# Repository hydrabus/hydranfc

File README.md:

HydraNFC Shield v1 and HydraNFC Antenna
========

HydraNFC hardware shield v1

The HydraNFC is an NFC shield hardware to sniff, read/write or emulate any 13.56MHz NFC tags for anyone interested in debugging/hacking/developing for NFC.
It has been designed to be used with HydraBus see https://github.com/hydrabus/hydrabus but can also be used with other MCU.

Open source code firmware(For HydraBus), is available see
https://github.com/hydrabus/hydrafw

Wiki for HydraFW: https://github.com/hydrabus/hydrafw/wiki

Tutorial with HydraBus + HydraNFC  (using HydraFW v0.5 beta):
* Initialize GPIO & SPI to communicate with TRF7970A/HydraNFC
* Initialize & read ISO15693/Vicinity Tag
* Initialize & read ISO14443A/Mifare Tag
* Use TRF7970A commands (SLOS743K – August 2011 – revised April 2014)
* For more details see 
https://github.com/hydrabus/hydrafw/wiki/HydraFW-HydraNFC-v1-guide
https://github.com/hydrabus/hydrafw/wiki/HydraFW-HydraNFC-v1.x-TRF7970A-Tutorial

Tutorial to use HydraNFC and understand how work the NFC chipset (TRF7970A) with BusPirate or any other hardware with SPI:
* See http://bvernoux.blogspot.fr/2012/01/nfc-ti-trf7970a-breakout-board-v10-for.html

For more details on the hardware see also http://hydrabus.com/hydranfc-1-0-specifications

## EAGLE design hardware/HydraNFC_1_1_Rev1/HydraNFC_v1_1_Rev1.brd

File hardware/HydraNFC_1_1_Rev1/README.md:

HydraNFC Shield Schematic and Board CadSoft Eagle 6.x
========

This directory contains HydraNFC shield Schematic and Board for CadSoft Eagle 6.x

HydraNFC shield: Hardware license [CC BY-NC 4.0](https://creativecommons.org/licenses/by-nc/4.0/) (for commercial license contact info@hydrabus.com)

For more details on the hardware see also http://hydrabus.com/?page_id=30

HydraNFC shield PCB Top

HydraNFC shield PCB Bottom

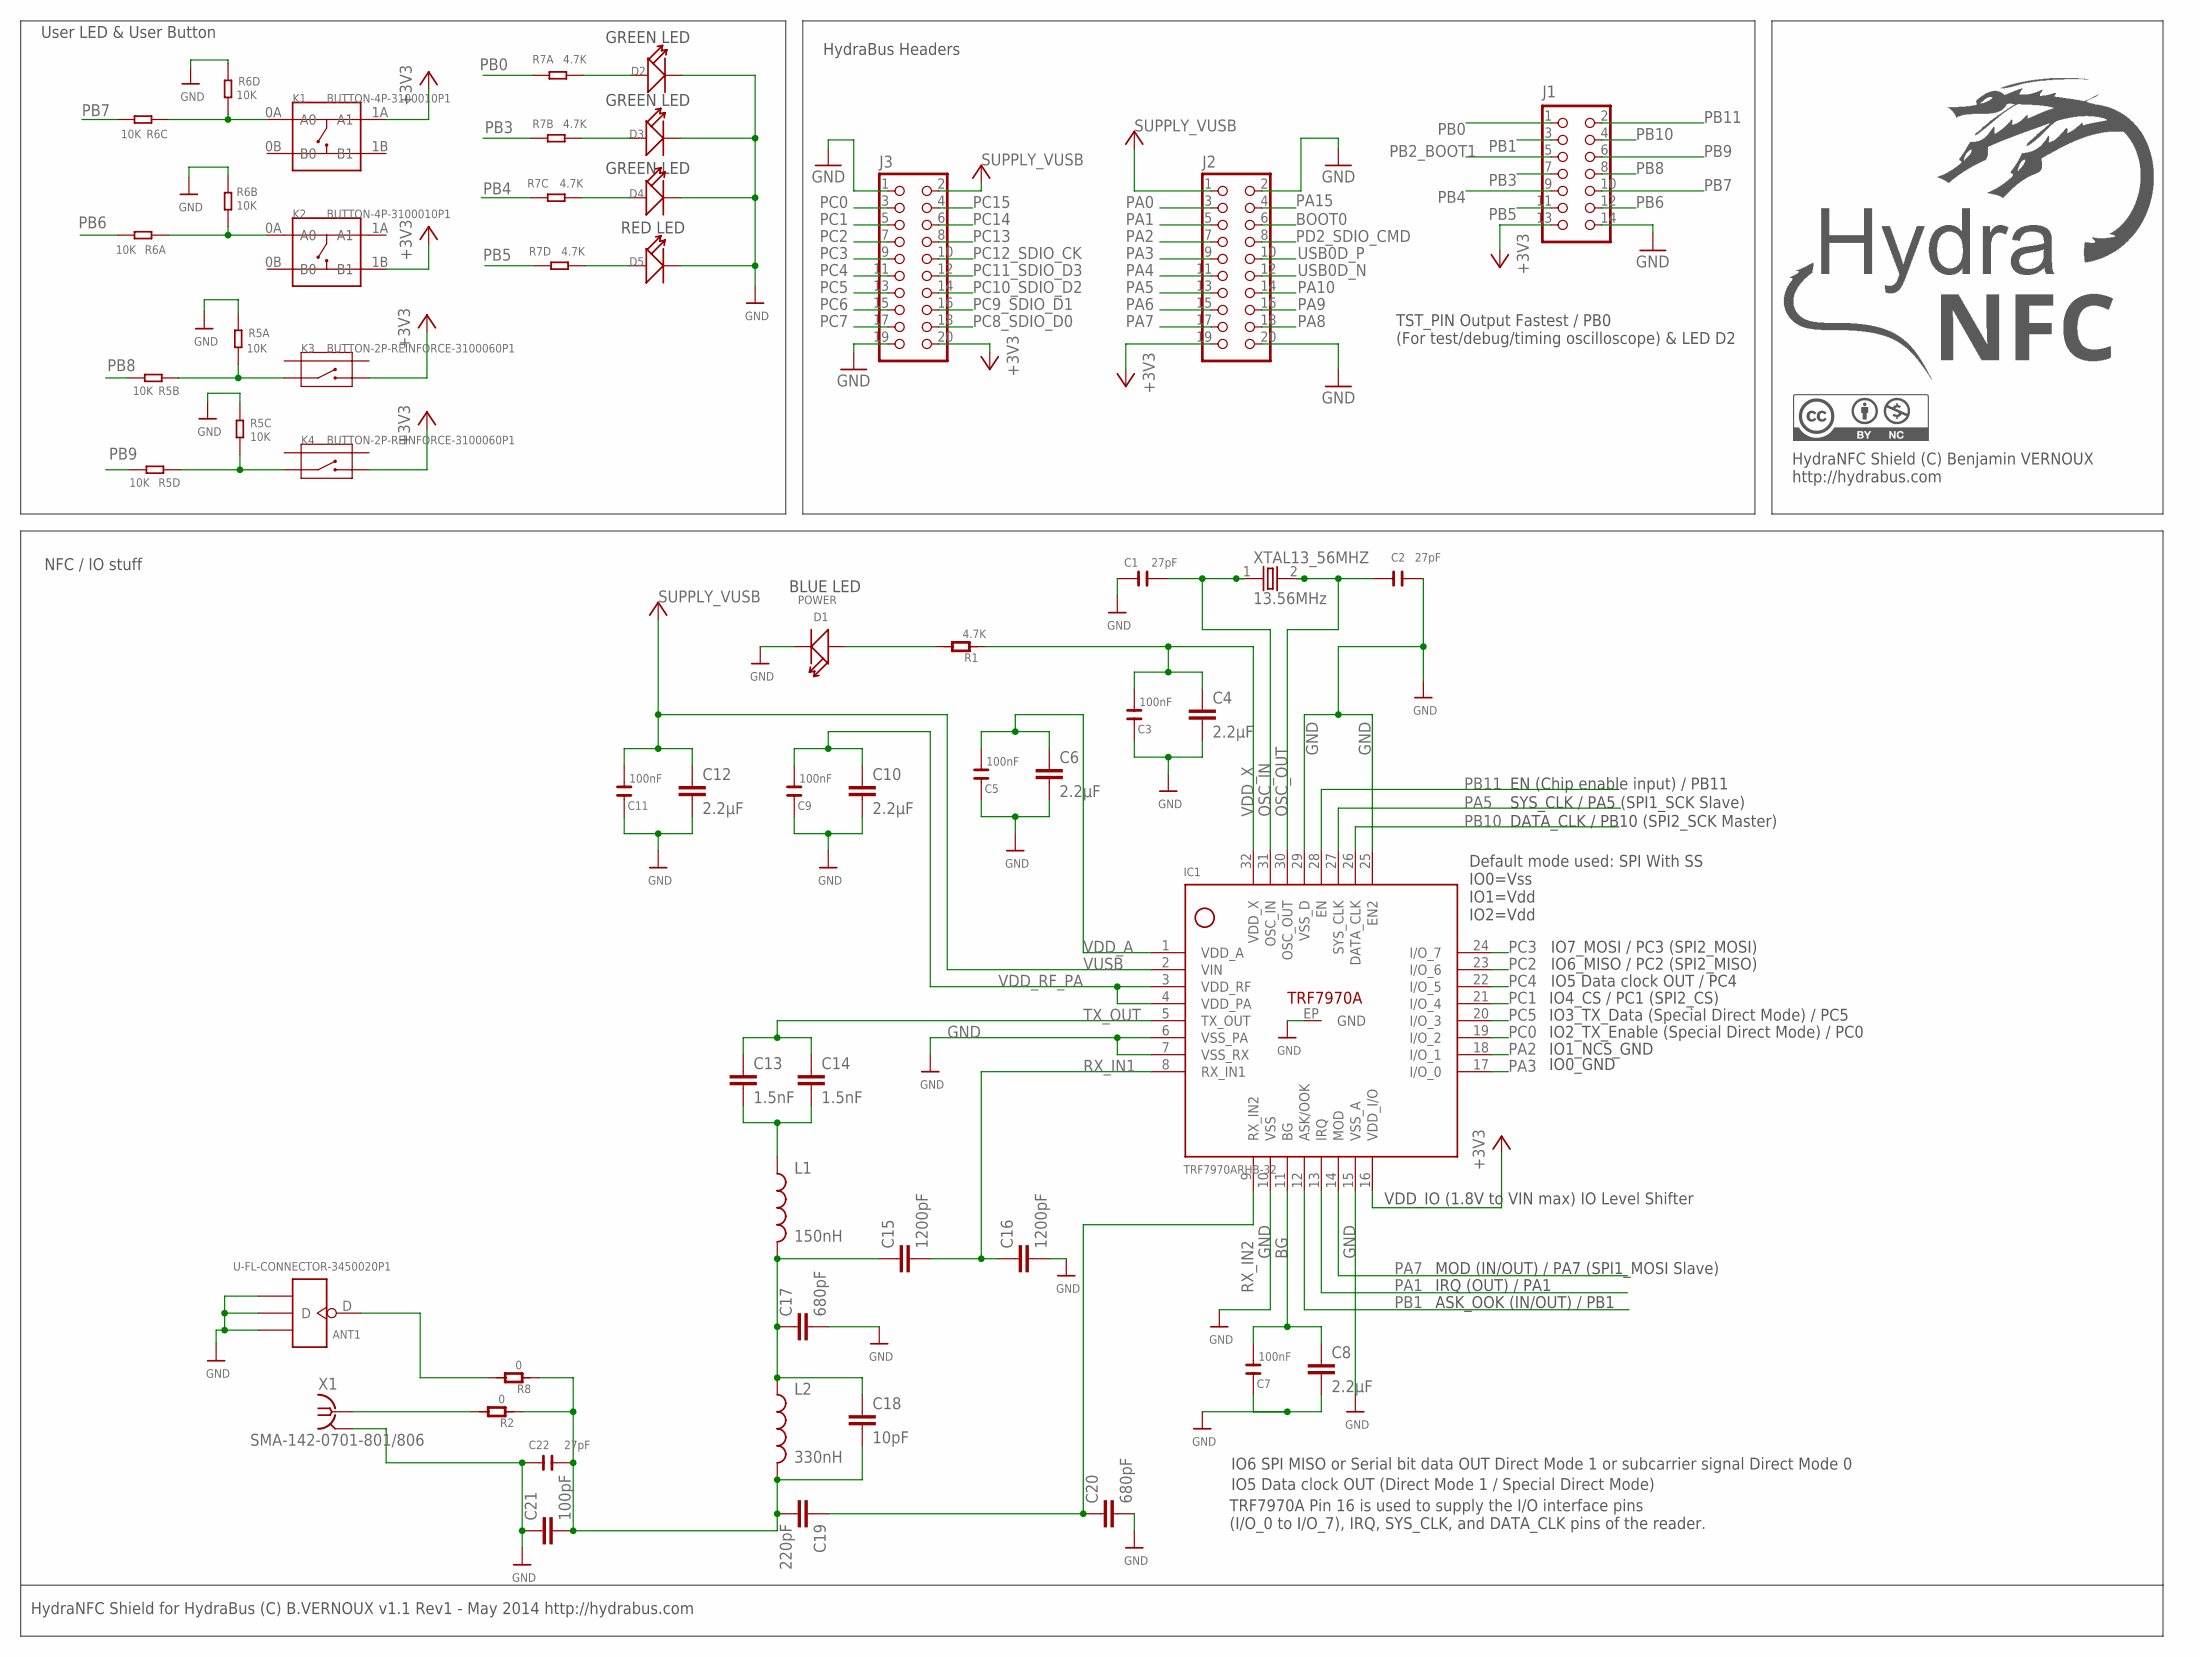
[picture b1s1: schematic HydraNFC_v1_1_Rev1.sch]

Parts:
ANT1: U-FL-CONNECTOR-3450020P1; U-FL
C1, C2, C22: 27pF; C0603
C3, C5, C7, C9, C11: 100nF; C0603
C4, C6, C8, C10, C12: 2.2µF; C805
C13, C14: 1.5nF; C805
C15, C16: 1200pF; C805
C17, C20: 680pF; C805
C18: 10pF; C805
C19: 220pF; C805
C21: 100pF; C805
D1: POWER; LED0603
D2, D3, D4, D5: LED; LED0603
IC1: TRF7970ARHB-32; TRF7970A
J1: HYDRABUS_SHIELD_CON_HEADER_2X07; HYDRABUS_SHIELD_M2X7
J2, J3: HYDRABUS_SHIELD_CON_HEADER_2X10; HYDRABUS_SHIELD_M2X10
K1, K2: BUTTON-4P-3100010P1; 4P-SMD-6.0X6.0X5.0H
K3, K4: BUTTON-2P-REINFORCE-3100060P1; 4P-SMD-7.0X3.5X3.5H-90D
L1: 150nH; 1210
L2: 330nH; 1210
R1: 4.7K; R0603
R2, R8: 0; R0603
R5, R6: 10K; R1206-8
R7: 4.7K; R1206-8
X1: SMA-142-0701-801/806; J502-ND-142-0701-801/806
XTAL13_56MHZ: 13.56MHz; HC-49U

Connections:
+3V3: IC1.16 (VDD_I/O), J1.13, J2.19, J3.20, K1.1A (A1), K2.1B (B1), K3.2, K4.2
BG: C7.2, C8.1, IC1.11 (BG)
BOOT0: J2.6
GND: ANT1.GND1, ANT1.GND2, ANT1.GND3, C1.1, C2.2, C3.1, C4.2, C5.1, C6.2, C7.1, C8.2, C9.1, C10.2, C11.1, C12.2, C16.2, C17.2, C20.2, C21.1, C22.2, D1.-, D2.-, D3.-, D4.-, D5.-, IC1.6 (VSS_PA), IC1.7 (VSS_RX), IC1.10 (VSS), IC1.15 (VSS_A), IC1.25 (EN2), IC1.29 (VSS_D), IC1.EP (GND), J1.14, J2.2, J2.20, J3.1, J3.19, R5.3 (1), R5.8 (2), R6.4 (1), R6.7 (2), X1.G@1 (GND), X1.G@2 (GND), X1.G@3 (GND), X1.G@4 (GND)
unnamed: C13.2, C14.2, L1.1
unnamed: C18.2, C19.2, C21.2, C22.1, L2.2, R2.2, R8.2
unnamed: C15.1, C17.1, C18.1, L1.2, L2.1
unnamed: D1.+, R1.1
unnamed: R2.1, X1.1
unnamed: K3.1, R5.1, R5.2 (1)
unnamed: K2.0A (A0), R6.2 (1), R6.8 (2)
unnamed: K4.1, R5.5 (2), R5.6 (2)
unnamed: K1.0A (A0), R6.3 (1), R6.5 (2)
unnamed: D2.+, R7.8 (2)
unnamed: D3.+, R7.7 (2)
unnamed: D4.+, R7.6 (2)
unnamed: D5.+, R7.5 (2)
unnamed: ANT1.D, R8.1
OSC_IN: C1.2, IC1.31 (OSC_IN), XTAL13_56MHZ.1
OSC_OUT: C2.1, IC1.30 (OSC_OUT), XTAL13_56MHZ.2
PA0: J2.3
PA1: IC1.13 (IRQ), J2.5
PA2: IC1.18 (I/O_1), J2.7
PA3: IC1.17 (I/O_0), J2.9
PA4: J2.11
PA5: IC1.27 (SYS_CLK), J2.13
PA6: J2.15
PA7: IC1.14 (MOD), J2.17
PA8: J2.18
PA9: J2.16
PA10: J2.14
PA15: J2.4
PB0: J1.1, R7.1
PB1: IC1.12 (ASK/OOK), J1.3
PB2_BOOT1: J1.5
PB3: J1.7, R7.2 (1)
PB4: J1.9, R7.3 (1)
PB5: J1.11, R7.4 (1)
PB6: J1.12, R6.1
PB7: J1.10, R6.6 (2)
PB8: J1.8, R5.7 (2)
PB9: J1.6, R5.4 (1)
PB10: IC1.26 (DATA_CLK), J1.4
PB11: IC1.28 (EN), J1.2
PC0: IC1.19 (I/O_2), J3.3
PC1: IC1.21 (I/O_4), J3.5
PC2: IC1.23 (I/O_6), J3.7
PC3: IC1.24 (I/O_7), J3.9
PC4: IC1.22 (I/O_5), J3.11
PC5: IC1.20 (I/O_3), J3.13
PC6: J3.15
PC7: J3.17
PC8_SDIO_D0: J3.18
PC9_SDIO_D1: J3.16
PC10_SDIO_D2: J3.14
PC11_SDIO_D3: J3.12
PC12_SDIO_CK: J3.10
PC13: J3.8
PC14: J3.6
PC15: J3.4
PD2_SDIO_CMD: J2.8
RX_IN1: C15.2, C16.1, IC1.8 (RX_IN1)
RX_IN2: C19.1, C20.1, IC1.9 (RX_IN2)
TX_OUT: C13.1, C14.1, IC1.5 (TX_OUT)
USB0D_N: J2.12
USB0D_P: J2.10
VDD_A: C5.2, C6.1, IC1.1 (VDD_A)
VDD_RF_PA: C9.2, C10.1, IC1.3 (VDD_RF), IC1.4 (VDD_PA)
VDD_X: C3.2, C4.1, IC1.32 (VDD_X), R1.2
VUSB: C11.2, C12.1, IC1.2 (VIN), J2.1, J3.2

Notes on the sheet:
HydraBus Headers
NFC / IO stuff
HydraNFC Shield for HydraBus (C) B.VERNOUX v1.1 Rev1 - May 2014 http://hydrabus.com
User LED & User Button
Default mode used: SPI With SS IO0=Vss IO1=Vdd IO2=Vdd
IO4_CS / PC1 (SPI2_CS)
IO6_MISO / PC2 (SPI2_MISO)
IO7_MOSI / PC3 (SPI2_MOSI)
IO5 Data clock OUT / PC4
IO3_TX_Data (Special Direct Mode) / PC5
IO1_NCS_GND
IO0_GND
IO2_TX_Enable (Special Direct Mode) / PC0
MOD (IN/OUT) / PA7 (SPI1_MOSI Slave)
DATA_CLK / PB10 (SPI2_SCK Master)
SYS_CLK / PA5 (SPI1_SCK Slave)
IRQ (OUT) / PA1
ASK_OOK (IN/OUT) / PB1
VDD_IO (1.8V to VIN max) IO Level Shifter
IO6 SPI MISO or Serial bit data OUT Direct Mode 1 or subcarrier signal Direct Mode 0
IO5 Data clock OUT (Direct Mode 1 / Special Direct Mode)
EN (Chip enable input) / PB11
TST_PIN Output Fastest / PB0 (For test/debug/timing oscilloscope) & LED D2
TRF7970A Pin 16 is used to supply the I/O interface pins (I/O_0 to I/O_7), IRQ, SYS_CLK, and DATA_CLK pins of the reader.
RED LED
GREEN LED
BLUE LED
HydraNFC Shield (C) Benjamin VERNOUX http://hydrabus.com

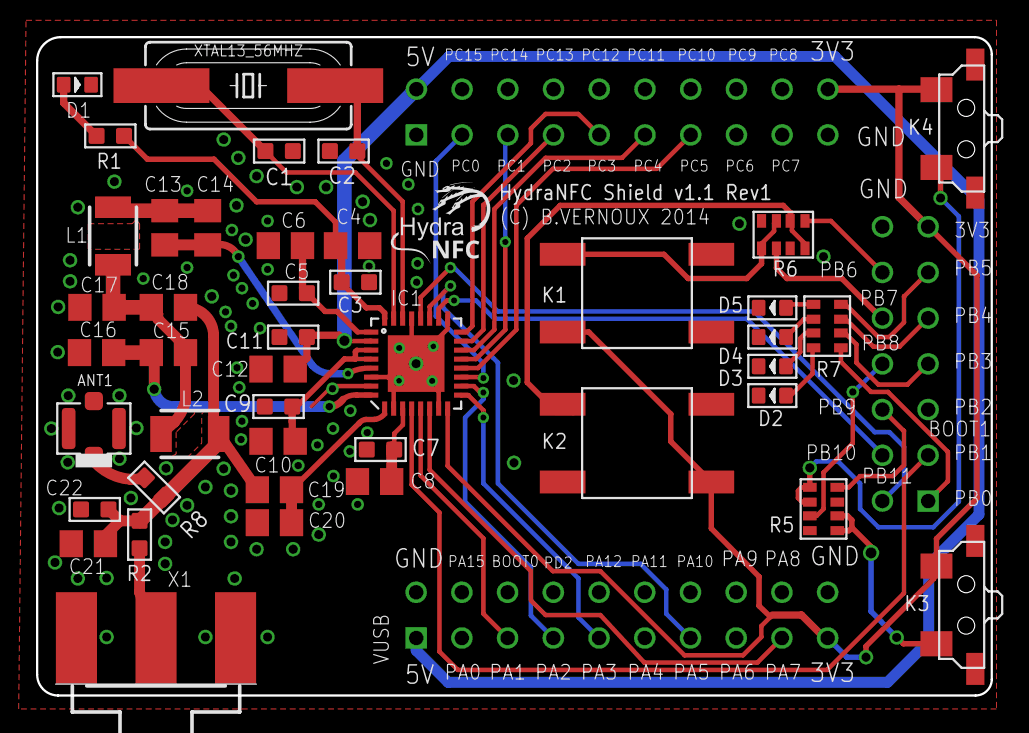
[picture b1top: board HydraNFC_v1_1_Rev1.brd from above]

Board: 2 copper layers, 53.0 x 36.6 mm, 46 parts (0 on the bottom side), 48 nets.

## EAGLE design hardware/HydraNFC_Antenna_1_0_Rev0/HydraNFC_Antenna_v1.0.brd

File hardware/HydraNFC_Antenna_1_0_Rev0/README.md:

HydraNFC Antenna Schematic and Board CadSoft Eagle 6.x
========

This directory contains HydraNFC Antenna Schematic and Board for CadSoft Eagle 6.x

HydraNFC Antenna: Hardware license [CC BY-NC 4.0](https://creativecommons.org/licenses/by-nc/4.0/) (for commercial license contact info@hydrabus.com)

For more details on the hardware see also http://hydrabus.com/?page_id=30

HydraNFC Antenna PCB Top

HydraNFC Antenna PCB Bottom

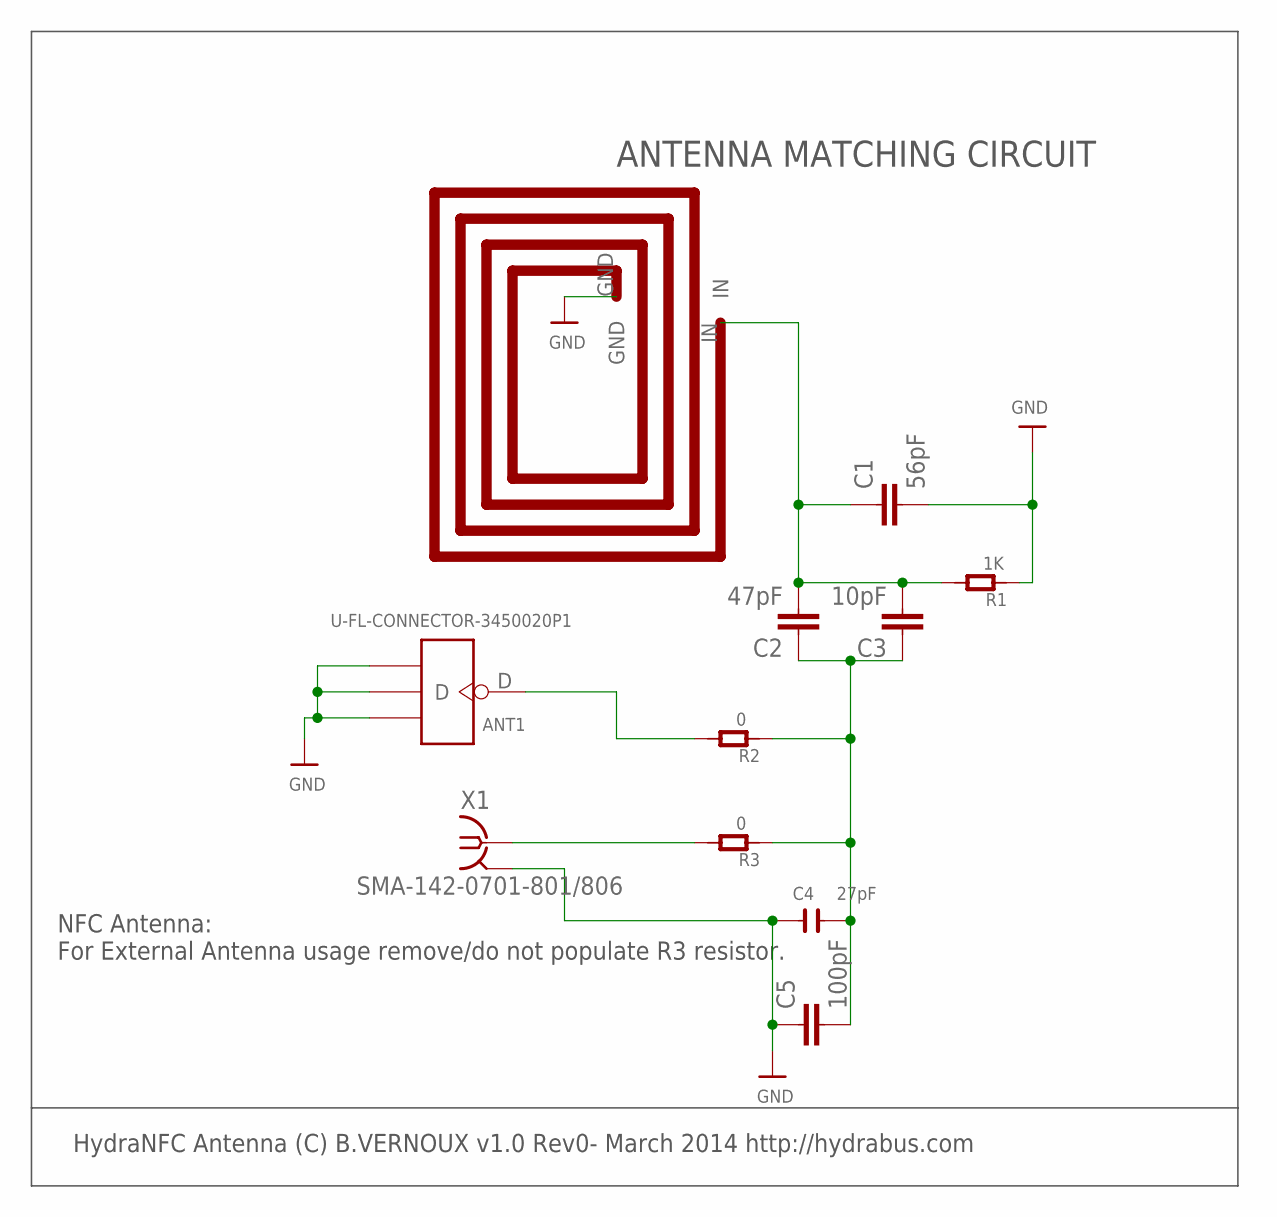
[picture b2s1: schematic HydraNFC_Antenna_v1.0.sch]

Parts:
ANT1: U-FL-CONNECTOR-3450020P1; U-FL
C1: 56pF; C805
C2: 47pF; C805
C3: 10pF; C805
C4: 27pF; C0603
C5: 100pF; C805
R1: 1K; R0603
R2, R3: 0; R0603
U$43: NFC_13_56MHz_ANTENNA; TRF7970A_ANTENNA
X1: SMA-142-0701-801/806; J502-ND-142-0701-801/806

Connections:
GND: ANT1.GND1, ANT1.GND2, ANT1.GND3, C1.2, C4.2, C5.1, R1.2, U$43.GND, X1.G@1 (GND), X1.G@2 (GND), X1.G@3 (GND), X1.G@4 (GND)
unnamed: C2.1, C3.1, C4.1, C5.2, R2.2, R3.2
unnamed: C1.1, C2.2, C3.2, R1.1, U$43.IN
unnamed: R3.1, X1.1
unnamed: ANT1.D, R2.1

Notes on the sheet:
HydraNFC Antenna (C) B.VERNOUX v1.0 Rev0- March 2014 http://hydrabus.com
ANTENNA MATCHING CIRCUIT
NFC Antenna: For External Antenna usage remove/do not populate R3 resistor.

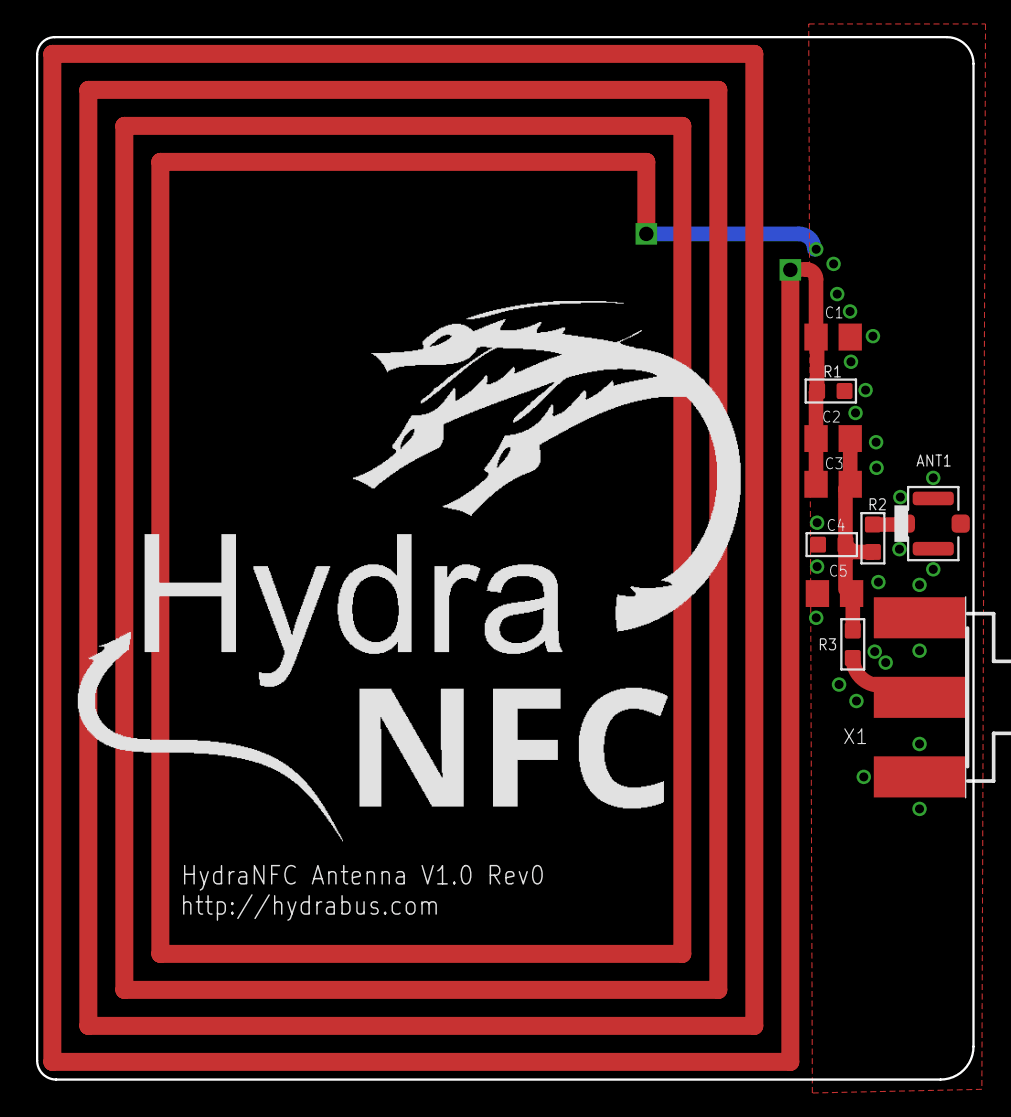
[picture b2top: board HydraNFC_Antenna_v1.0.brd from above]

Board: 2 copper layers, 52.0 x 57.9 mm, 11 parts (0 on the bottom side), 5 nets.

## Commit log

2014-07-20 HydraNFC Board
2014-07-24 HydraNFC Hardware Pins and Modes and PinOut
2014-08-08 Update board photo
2014-09-11 HydraNFC hardware files Eagle, PDF, xls ...
2014-09-11 Update image smaller
2014-10-10 Update HydraFW link
2014-10-11 Added link to Wiki HydraFW
2016-03-28 Updated HydraNFC_modes_and_pinout.pdf towards Special Direct Mode(SDM) & Direct Mode 1(DM1) added LibreOffice HydraNFC_modes_and_pinout.odg
2016-05-25 Add HydraNFC_LogicAnalyzer documents (LibreOffice ODS & PDF)
2016-12-18 Update of links replaced bvernoux by hydrabus
2017-08-01 Fixed Typo in Schematic/BOM Description for Decoupling Capacitor C3 & C5 & C7 & C9 & C11 which are 100nF (wrong value was 0.01uF so 10nF)
2019-11-25 Clarified Direct Mode
2020-01-25 Update links to HydraNFC-v1
2022-09-21 Clarification of version
2026-01-31 Remove purchase link from README
    Removed purchase link for HydraBus/HydraNFC from README.
